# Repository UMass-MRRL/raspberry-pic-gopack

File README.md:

# RaspberryPIC GoPack

The GoPack is a universal control/driver pack meant for rapid prototyping of mechatronic systems. 
It houses a **Raspberry Pi Version 3 Model B**, 16 bit dsPIC33F microcontroller, and has various analog and digital inputs and outputs. Programming the GoPack is done in **MATLAB Simulink version 2017b**, and sent wirelessly through the WLAN to the Raspberry Pi.

Last updated: 12/04/2017

For the most up-to-date Setup guide (Raspberry Pi Version 3 Model B with MATLAB Simulink version 2017b) please click: https://github.com/UMass-MRRL/raspberry-pic-gopack/tree/master/GoPack%20v2.0%20-%20Pi%203%20Simulink%20r2017b

If you are using the Raspberry Pi 2 Model B with MATLAB Simulink version 2015b, then please click: https://github.com/UMass-MRRL/raspberry-pic-gopack/tree/master/GoPack%20v1.0%20-%20Pi%202%20Simulink%20r2015b

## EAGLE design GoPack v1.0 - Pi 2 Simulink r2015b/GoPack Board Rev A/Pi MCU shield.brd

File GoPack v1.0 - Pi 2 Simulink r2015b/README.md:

# RaspberryPIC GoPack v1.0

The GoPack is a universal control/driver pack meant for rapid prototyping of mechatronic systems. 
It houses a **Raspberry Pi Version 2 Model B**, 16 bit dsPIC33F microcontroller, and has various analog and digital inputs and outputs. Programming the GoPack is done in **MATLAB Simulink version 2015b**, and sent wirelessly through the WLAN to the Raspberry Pi.

Last updated: 02/23/2017

## Raspberry Pi Setup: 

### 1) Installing support packages: (for starting from scratch)
The RaspberryPi boots off of an SD card with the MATLAB Support Package and operating system installed.  The MATLAB support packages and are downloaded in MATLAB, and written to the Pi with a USB SD reader/writer. All remaining programming is done over wifi. The package can be found in MATLAB under Add-Ons drop-down. Choose install from internet, choose Raspberry Pi, check all packages available for Pi, and follow the instructions. You will be guided to install your micro SD card in the USB card reader, and install the Rapberry Pi OS “Raspbian” with Matlab support packages for the appropriate Pi model. The latest version of GoPack uses Pi 2 Model B. 
.  
### 2) Booting the Pi up:
Before booting the GoPack, install the SD card that you installed the Raspbian OS on connect any USB peripherals that will be needed before booting so that the RaspberryPi recognizes them. Boot the Pi by plugging in a micro USB power source.

### 3) WLAN setup: 
The easiest way to set up a WLAN is to use a router connected to the PC used for MATLAB. You must boot the RaspberryPi with a mouse, keyboard, WIFI dongle and HDMI monitor to set up the WLAN to connect automatically. Have the PC hosting MATLAB connected to the router, and the router to the main ethernet. In the Pi Rasbian OS, select Menu>Preferences>Wifi Configuration. Here you setup your network. Scan for Networks and choose the WLAN that the main PC is connected to. Double click, enter the password security key and click Add then close the scan window. In wpa_gui click connect. It should connect at this time. Make note of the following: SSID, BSSID, and IP address.

Once the connection is setup, the following boot ups are done with only the peripherals needed, and it should connect to the WLAN automatically. For the GoPack, all you need is the wifi dongle. Now shutdown the Pi by going to Menu. When the green light on the PI stops flashing, unplug the keyboard and monitor, and reboot by disconnecting and connecting the micro USB power source. 

### 4) Connecting to Pi with SSH from the main computer: 
Now on the PC, you need to be able to log in via SSH to have access to the Pi command prompt over the WLAN. Here you can download an executable called “Putty” to do so. http://www.chiark.greenend.org.uk/~sgtatham/putty/download.html
Save the executable in an accessible location, you will use it frequently. 
Run Putty. Click connection on the tree, and change “Seconds between keepalives” to 30 in order to keep the connection from timing out. Click Session in the tree, type in the IP address, highlight defaulty and save. You can now click open, and it will save the IP for next time. If you get a security alert, click yes. The default username and password are pi and raspberry (note the password will not show in the command window). 

### 5) Installing GPIO Interface Library wiringPi
The driver blocks used for PWM, ADC and Encoder inputs use the library called wiringPi www.wiringpi.com. To install wiringPi, git must first be installed. 
Boot the Pi and establish a SSH connection. Type:

`sudo apt-get install git-core`

If any errors happen, reinstall raspbian through MATLAB for the most updated copy. You can now download wiringPi. 

`git clone https://github.com/UMass-MRRL/wiringPi-GoPack.git`

Note: If you download wiringPi from its original source (git://git.drogon.net/wiringPi), that’s the wrong version. If updating wiringPi, type:
```
cd wiringPi-GoPack
git pull origin
```

Shutting the Pi down:
When connected with SSH via Putty, type this to shut down safely.  

`sudo halt`

Click OK when Putty gives a fatal error, it thinks the connection has failed. Close Putty. 

## Interfacing the Raspberry Pi with the GoPack add-on board

### 1) Initializing the GoPack board
The GoPack board runs on a dsPIC33F microcontroller. A set of pins is provided for programming and debugging the microcontroller should you wish to modify the firmware. For the initial setup, ensure that the board is receiving power. 

**Note: Do not supply power through the GoPack terminals and the micro-USB connector on the Raspberry Pi at the same time.** The current iteration of the board does not have back-current protections should these 5V levels be slightly different.

With the board powered up, flash the microcontroller with the provided files using a PICkit3 or similar device. You can build, edit, and download this project to the hardware from within MPLAB, or program it directly with the provided .hex files. A bright red status LED should come on if the microcontroller is running successfully.

### 2) Interfacing with the Raspberry Pi
The only physical assembly required is mating the 40 pin male connector on the Raspberry Pi with the GoPack 40-pin female connector. The boards should stack directly on top of each other. The Raspberry Pi will receive power through this connection from the GoPack board. It is recommended to use standoffs between the boards to support the cantilevered end.

## Using GoPack with MATLAB and Simulink

### 1) Configure Simulink to run models on Raspberry Pi hardware
For Simulink to run models on the Raspberry Pi, it must be configured to run on external hardware. Enter the "Configuration Parameters" dialog and locate the "Hardware Implementation" tab. "Raspberry Pi" should be available on the "Hardware board" dropdown menu. Set the IP address for the Host name, supply the username and password for the Raspberry Pi, and set the Build directory to "/home/pi".

In the Solver tab, set the Solver options to discrete and fixed-step. Set the desired control loop sample time in the "Fixed step size (fundamental sample time)" field in seconds. (i.e. input a value of 0.001 for a 1 ms sample time).

In the Simulink model window, type "inf" for the simulation time, and set the mode to "external".

To run a model on the Raspberry Pi to view data and adjust the model in real-time, press the 'play' arrow button. To send a model to the Raspberry Pi to run independently of the host PC, click "Deploy to Hardware" on the far right of the control bar.

The Simulink blocks included in this repository use the WiringPi library to access Raspberry Pi functions not included in the standard blocks included with the Mathworks toolbox - control over SPI communication specifically.

### 3) Configure Simulink for compatibility with WiringPi functions
WiringPi will not work unless you add “-lwiringPi” to the linker flags in the simulink makefile. To do this, in your simulink model, go to Model Properties->Model Properties->Callbacks->PreSaveFcn and add the line:

`set_param(gcs,'PostCodeGenCommand','setBuildArgs(buildInfo)');`

Make sure that setBuildArgs.m is included in the active directory. This file is included in the Simulink Scripting section of this repository.

### 4) Using GoPack s-Functions to handle sensors and actuators
It is recommended that you familiarize yourself with the basics:
http://www.mathworks.com/help/supportpkg/raspberrypi/examples/getting-started-with-raspberry-pi-hardware.html

Three Simulink s-Function blocks are provided to allow the Simulink model to access sensor readings and dictate actuator outputs. 

The "inputs_to_SPI_bytes" block converts float or integer inputs into bytes for serial transfer. This primarily means motor duty cycle or voltage input. It also formats requests for readings from specific sensors.

The "SPI" block simply performs an SPI transfer of the byte vector assembled by the previous block. The output is a byte vector of requested sensor readings, and loopback confirmation of the requested outputs.

The "SPI_bytes_to_outputs" block converts the received byte vector into float or integer values for the requested sensor readings and looped-back outputs. Depending on the amount of samples the sensor is configured to perform per Simulink loop, outputs corresponding with each separate sensor reading can be a vector containing multiple samples. Filtering, chronological arrangement of this data, or averaging are left to the user to perform with standard Simulink blocks as needed.

Note that a single sample delay function is required before the input to the serial transfer subsystem made up of these three blocks. The model will form an algebraic loop and will not run if the delay is not included.

It is recommended to use the provided PID position control model for reference. It uses encoder feedback (500 counts/turn) to drive a DC motor while logging data from 5 simultaneous analog inputs. This controller was successfully tested with a Maxon EC30 motor using an ESCON 50/5 motor driver.

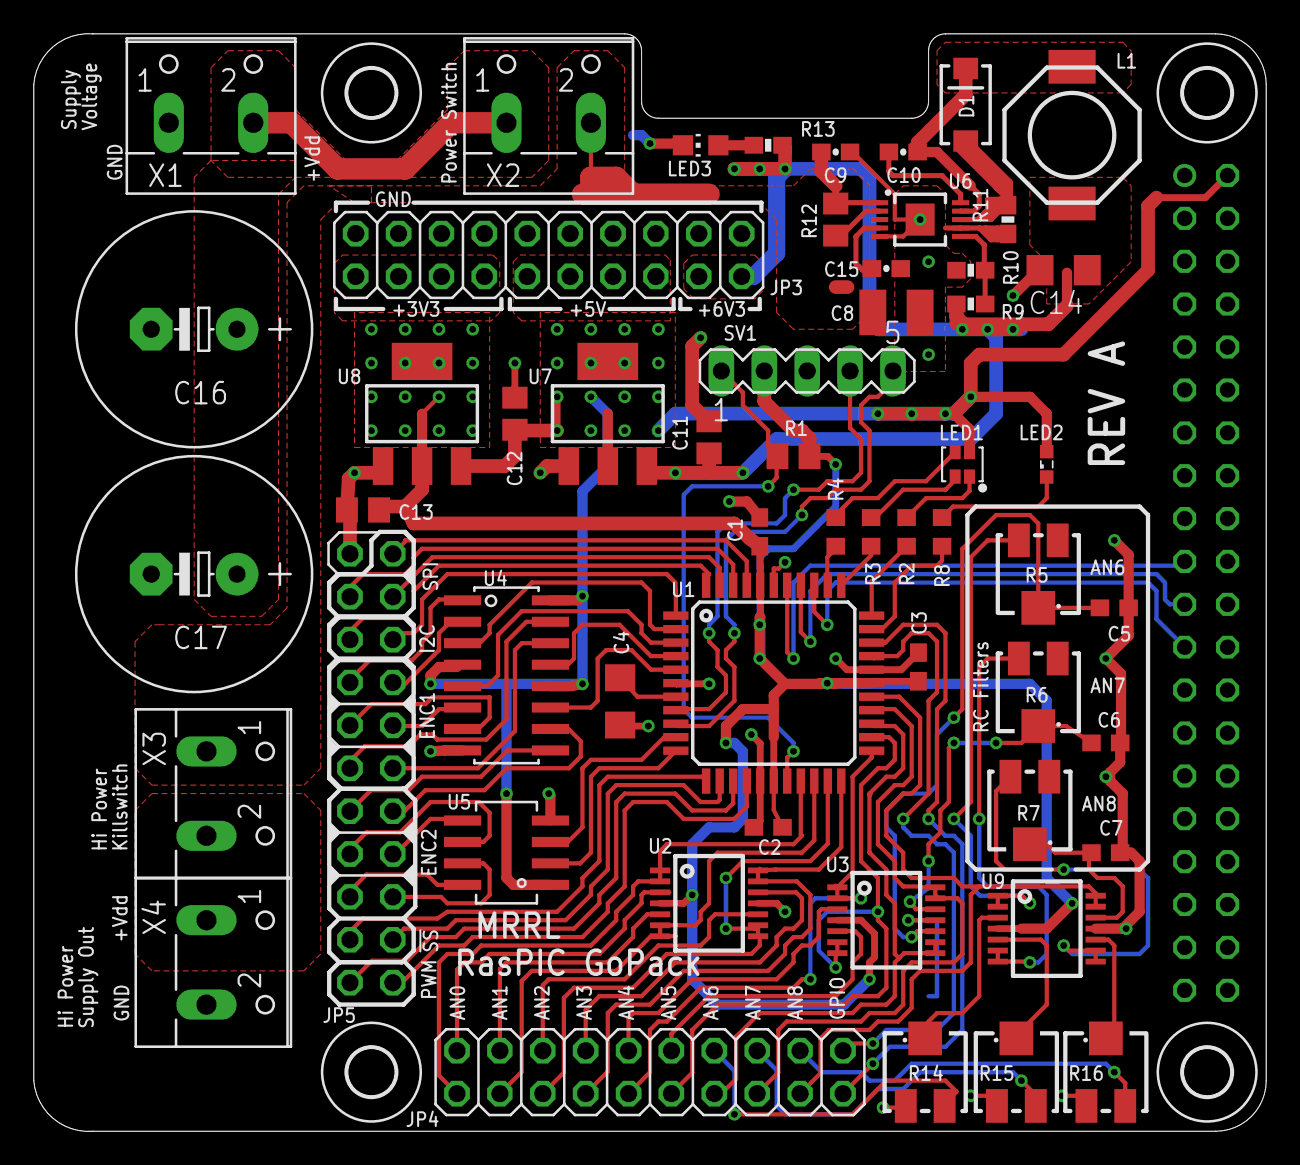
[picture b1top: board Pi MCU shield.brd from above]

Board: 2 copper layers, 73.0 x 65.0 mm, 60 parts (1 on the bottom side), 85 nets.

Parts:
C1, C2, C3: 0.1uF; C0603
C4, C14: 10uF; C1206
C5, C6, C7: 0.47uF; C0603
C8: 4.7uF; C1210
C9, C10: .1uF; 0603-CAP
C11, C12, C13: 10uF; C0805
C15: .022uF; 0603-CAP
C16, C17: E5-13
D1: B340A; SMA-DIODE
H1, H2, H3, H4: MOUNT-HOLE2.8; 2,8
JP3: Supply Pins; 2X10
JP4: Analog-GPIO; 2X10
JP5: Peripherals; 2X11
L1: CDRH8D38
LED1: LTST-C19HE1WT; 0606
LED2: Yellow; SML0603
LED3: GRN; CHIP-LED0805
R1: 10k; R0805
R2, R8: 1k; R0603
R3, R4: 470; R0603
R5, R6, R7, R14, R15, R16: 50k; RTRIM3224J
R9: 4.7k; 0603-RES
R10: 3k; 0603-RES
R11: .08; 0603-RES
R12: 240k; R0805
R13: 390; 0603-RES
SV1: Programmer; MA05-1
SV2: RPI; FE20-2
U1: DSPIC33FJ64MC204TQFP; TQFP44
U2, U3, U9: LMH6644MT; TSSOP14
U4: MC3846D; SO-16
U5: UA9637AC; SO-08
U6: LM25011; HVSS0P-10
U7: 5V Reg; SOT223
U8: 3V3 Reg; SOT223
X1: Supply; W237-102
X2: Pwr Switch; W237-102
X3: Motor Kill; W237-102
X4: Motor Supply; W237-102

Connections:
!A1: JP5.7, U4.1
!A2: JP5.13, U4.9
!B1: JP5.9, U4.7
!B2: JP5.15, U5.6
!I1: JP5.11, U4.15
!I2: JP5.17, U5.8
!MCLR: R1.1, SV1.1, U1.18
+3V3: C1.1, C2.1, C3.1, C13.1, JP3.1, JP3.3, JP3.5, JP3.7, R1.2, SV1.2, U1.17, U1.28, U1.40, U2.4, U3.4, U8.2, U8.4, U9.4
+5V: C12.1, JP3.9, JP3.11, JP3.13, JP3.15, LED1.4, LED2.A, SV2.2, U4.4, U4.12, U4.16, U5.1, U7.2, U7.4, U8.3
+6V3: C11.1, C14.1, JP3.17, JP3.19, L1.P$2, R9.2, R13.2, U7.3
A1: JP5.8, U4.2
A2: JP5.14, U4.10
AN0: JP4.20, U1.19, U2.1, U2.2
AN1: JP4.18, U1.20, U2.6, U2.7
AN2: JP4.16, U1.21, U2.8, U2.9
AN3: JP4.14, U1.22, U2.13, U2.14
AN4: JP4.12, U1.23, U3.1, U3.2
AN5: JP4.10, U1.24, U3.6, U3.7
AN6: JP4.8, U1.25, U3.8, U3.9
AN7: JP4.6, U1.26, U3.13, U3.14
AN8: JP4.4, U1.27, U9.13, U9.14
A_IN0: JP4.19, U2.3
A_IN1: JP4.17, U2.5
A_IN2: JP4.15, U2.10
A_IN3: JP4.13, U2.12
A_IN4: JP4.11, U3.3
A_IN5: JP4.9, U3.5
A_IN6: JP4.7, R14.3
A_IN7: JP4.5, R15.3
A_IN8: JP4.3, R16.3
B1: JP5.10, U4.6
B2: JP5.16, U5.5
BLUE: LED1.2, R3.1
CS0: JP5.19, U1.12
CS1: JP5.20, U1.13
GND: C1.2, C2.2, C3.2, C4.2, C5.2, C6.2, C7.2, C8.2, C9.1, C11.2, C12.2, C13.2, C14.2, C15.2, C16.-, C17.-, JP3.2, JP3.4, JP3.6, JP3.8, JP3.10, JP3.12, JP3.14, JP3.16, JP3.18, JP3.20, JP5.1, LED3.C, R10.1, R11.1, R14.1, R15.1, R16.1, SV1.3, SV2.6, SV2.9, SV2.14, SV2.20, SV2.25, SV2.30, SV2.34, SV2.39, U1.6, U1.16, U1.29, U1.39, U2.11, U3.11, U4.8, U5.4, U6.5, U6.7, U6.PAD, U7.1, U8.1, U9.11, X1.1, X4.2
GPIO1: JP4.1, U1.30
GPIO2: JP4.2, U1.31
GREEN: LED1.3, R4.1
I1: JP5.12, U4.14
I2: JP5.18, U5.7
INDX1: U1.4, U4.13
INDX2: U1.10, U5.3
MISO: SV2.21, U1.37
MOSI: SV2.19, U1.38
unnamed: R15.2, U9.5
unnamed: C4.1, U1.7
unnamed: C8.1, C9.2, R12.2, U6.1, X2.2, X3.1
unnamed: C7.1, R7.2, U9.12
unnamed: C5.1, R5.2, U3.10
unnamed: X3.2, X4.1
unnamed: R14.2, U9.3
unnamed: R6.3, U9.6, U9.7
unnamed: R7.3, U9.8, U9.9
unnamed: LED3.A, R13.1
unnamed: LED2.C, R8.2
unnamed: R4.2, U1.35
unnamed: R3.2, U1.34
unnamed: R2.2, U1.33
unnamed: R16.2, U9.10
unnamed: R8.1, U1.32
unnamed: C10.1, D1.C, L1.P$1, U6.9
unnamed: R9.1, R10.2, U6.6
unnamed: R12.1, U6.2
unnamed: C15.1, U6.4
unnamed: D1.A, R11.2, U6.8
unnamed: C10.2, U6.10
unnamed: R5.3, U9.1, U9.2
unnamed: C6.1, R6.2, U3.12
OC1: JP5.21, U1.14
OC2: JP5.22, U1.15
PGEC: SV1.5, U1.9
PGED: SV1.4, U1.8
QEA1: U1.2, U4.3
QEA2: U1.5, U4.11
QEB1: U1.3, U4.5
QEB2: U1.11, U5.2
RED: LED1.1, R2.1
SCK: SV2.23, U1.36
SCK2: JP5.2, U1.41
SCL1: JP5.5, U1.44
SDA1: JP5.6, U1.1
SDI2: JP5.3, U1.42
SDO2: JP5.4, U1.43
VDD: C16.+, C17.+, X1.2, X2.1

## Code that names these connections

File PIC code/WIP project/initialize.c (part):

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//		RB2 - AN4               (PIN23) input
//		RB3 - AN5               (PIN24) input      
//		RB4 - RGB Red           (PIN33) 
//		RB5 - SCK2 (SPI2 master)(PIN41)
//		RB6 - SDI2 (SPI2 master)(PIN42) input
//		RB7 - SDO2 (SPI2 master)(PIN43)
//		RB8 - SCL1 (I2C)        (PIN44)
//		RB9 - SDA1 (I2C)        (PIN1)
//		RB10 - Program (PGED2)  (PIN8)
//		RB11 - Program (PGEC2)  (PIN9)
//		RB12 - INDX2 (ENC2)     (PIN10)	input
//		RB13 - QEB2 (ENC2)      (PIN11) input
//		RB14 - OC1   		    (PIN14)
//		RB15 - OC2		        (PIN15)     
//		RC0	- AN6				(PIN25) input
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//		RC3 - SCK1 (SPI1 slave) (PIN36) input
//		RC4 - SDO1 (SPI1 slave) (PIN37)
//		RC5 - SDI1 (SPI1 slave) (PIN38) input
//		RC6 - QEA1 (ENC1)       (PIN2)  input
//		RC7 - QEB1 (ENC1)       (PIN3)  input
//		RC8 - INDX1 (ENC1)      (PIN4)  input
//		RC9 - QEA2 (ENC2)       (PIN5)  input
*/ 

{
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    QEI1CONbits.POSRES = 1;     //Index pulse resets position counter (only applies when QEIM = 4 or 6)
    DFLT1CONbits.IMV = 0;       //A and B input signals both 0 for match on index pulse
    DFLT1CONbits.QEOUT = 0;     //Digital filter outputs are disabled (normal pin operation)
    DFLT1CONbits.QECK = 3;      //1:16 Clock divide for QEA1/QEB1/INDX1
    POS1CNT = 0;
    MAX1CNT = ENC1_RES-1; 
    
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
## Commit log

2017-01-18 Additional S-function scripts
2017-02-23 Update readme to include setup information.
2017-02-23 Expanded to include Simulink setup
2017-02-24 Added PID position control example
2017-02-24 Updated encoder handling, updated s-Functions
2017-02-24 Updated board files 2-24-17
2017-02-24 Cleanup 2-24-17
2017-02-24 Microcontroller programming instructions added
2017-02-24 Release build firmware added 2-24-17
2017-02-24 Added Creo models
2017-02-24 Removed redundant models
2017-02-24 Board updates
2017-03-22 Parts list added
2017-03-22 Updated parts list
2017-03-30 PIC code updated
2017-03-30 Experimenting with message size
2017-10-24 Test Commit. Also, added a sample project for 2017
2017-10-24 Edited README to reflect the new procedure
2017-11-27 Added version 1 information to the ReadMe
2017-11-27 Updated board files
2017-12-03 Rearranging directories
2017-12-03 Differentiating READMEs
2017-12-03 README links
2017-12-03 Readme
2017-12-03 Readme editing
2017-12-03 Test Readme
2017-12-03 Testing relativelinks
2017-12-03 test

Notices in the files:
parts and their libraries:
SparkFun-Capacitors: Licensing: Creative Commons ShareAlike 4.0 International - https://creativecommons.org/licenses/by-sa/4.0
